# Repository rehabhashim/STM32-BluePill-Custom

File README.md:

# STM32-BluePill-Custom
KiCad project for a custom STM32F103C8T6 (Blue Pill) development board. The PCB layout focuses on practical hardware design principles, including power integrity, ground planes, and DFM rules.

Key technical details:

The design centers on the STM32F103C8T6 (ARM Cortex-M3) microcontroller driven by a 16MHz external crystal. For robust power distribution, I implemented solid copper pours for the VBUS and +3.3V nets to improve thermal and current handling, backed by a continuous GND pour across the board to ensure a solid return path and minimize EMI. Signal integrity was prioritized by placing individual 100nF decoupling capacitors directly at the MCU's VDD pins to reduce loop inductance, alongside a dedicated VDDA filter network utilizing a 120Ω ferrite bead and capacitors for clean ADC performance. Mechanically, the board's outline and edge cuts were explicitly engineered to properly overhang the USB-B Mini connector, preventing any physical clearance issues post-fabrication.

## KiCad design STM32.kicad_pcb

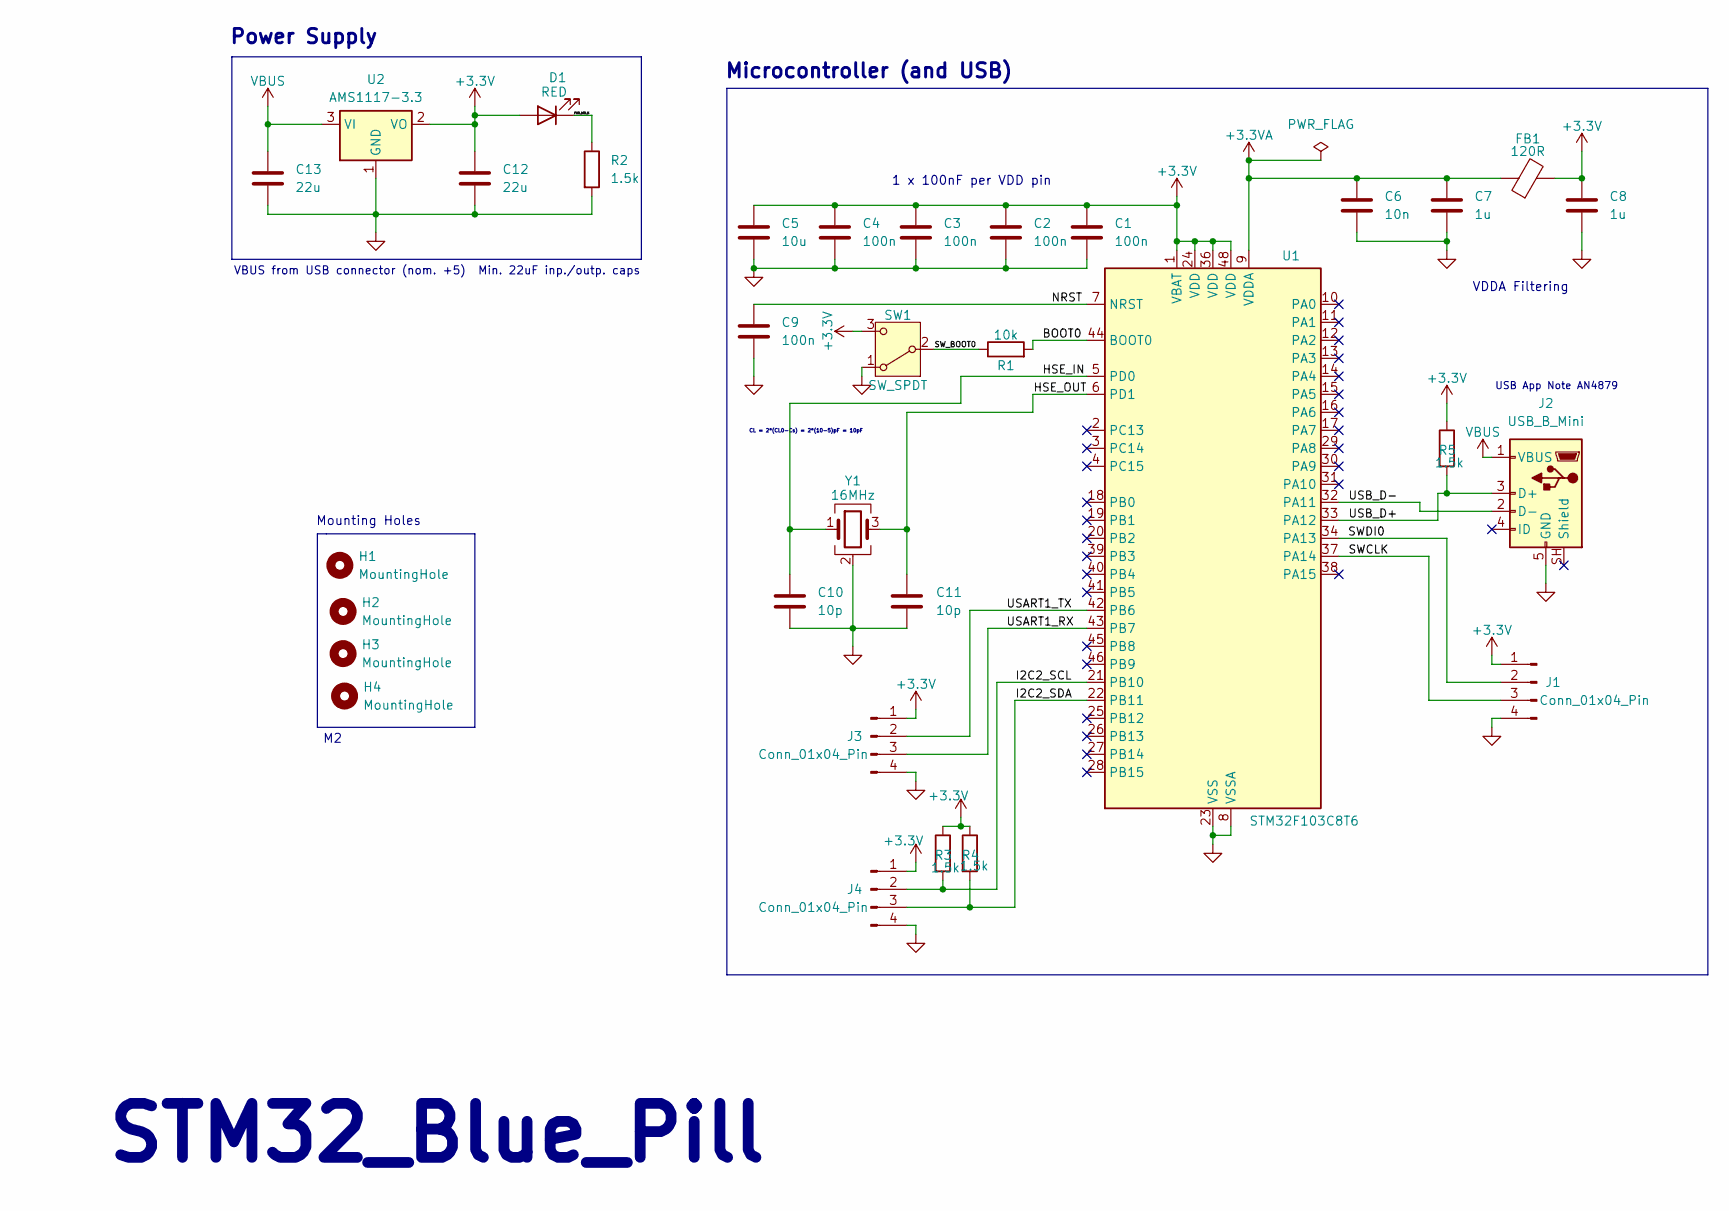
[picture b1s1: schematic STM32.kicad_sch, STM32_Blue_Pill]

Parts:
C1, C2, C3, C4, C9: 100n; C_0402_1005Metric
C5: 10u; C_0603_1608Metric
C6: 10n; C_0402_1005Metric
C7, C8: 1u; C_0402_1005Metric
C10, C11: 10p; C_0402_1005Metric
C12, C13: 22u; C_0805_2012Metric
D1: RED; LED_0603_1608Metric
FB1: 120R; L_0603_1608Metric
H1, H2, H3, H4: MountingHole; MountingHole_2.2mm_M2
J1, J3, J4: Conn_01x04_Pin; PinHeader_1x04_P2.54mm_Vertical
J2: USB_B_Mini; USB_Mini-B_Wuerth_65100516121_Horizontal
R1: 10k; R_0402_1005Metric
R2, R3, R4, R5: 1.5k; R_0402_1005Metric
SW1: SW_SPDT; SW_SPDT_PCM12
U1: STM32F103C8T6; LQFP-48_7x7mm_P0.5mm
U2: AMS1117-3.3; SOT-223-3_TabPin2
Y1: 16MHz; Crystal_SMD_3225-4Pin_3.2x2.5mm

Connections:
+3.3V: C1.1, C2.1, C3.1, C4.1, C5.1, C8.1, C12.1, D1.2 (A), FB1.2, J1.1, J3.1, J4.1, R3.1, R4.1, R5.1, SW1.3 (C), U1.1 (VBAT), U1.24 (VDD), U1.36 (VDD), U1.48 (VDD), U2.2 (VO)
+3.3VA: C6.1, C7.1, FB1.1, U1.9 (VDDA)
/BOOT0: R1.2, U1.44 (BOOT0)
/HSE_IN: C10.1, U1.5 (PD0), Y1.1
/HSE_OUT: C11.1, U1.6 (PD1), Y1.3
/I2C2_SCL: J4.2, R3.2, U1.21 (PB10)
/I2C2_SDA: J4.3, R4.2, U1.22 (PB11)
/NRST: C9.1, U1.7 (NRST)
/PWR_LED_K: D1.1 (K), R2.1
/SWCLK: J1.3, U1.37 (PA14)
/SWDI0: J1.2, U1.34 (PA13)
/SW_BOOT0: R1.1, SW1.2 (B)
/USART1_RX: J3.3, U1.43 (PB7)
/USART1_TX: J3.2, U1.42 (PB6)
/USB_D+: J2.3 (D+), R5.2, U1.33 (PA12)
/USB_D-: J2.2 (D-), U1.32 (PA11)
GND: C1.2, C2.2, C3.2, C4.2, C5.2, C6.2, C7.2, C8.2, C9.2, C10.2, C11.2, C12.2, C13.2, J1.4, J2.5 (GND), J3.4, J4.4, R2.2, SW1.1 (A), U1.8 (VSSA), U1.23 (VSS), U1.35 (VSS), U1.47 (VSS), U2.1 (GND), Y1.2 (G), Y1.4 (G)
VBUS: C13.1, J2.1 (VBUS), U2.3 (VI)

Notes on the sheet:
Microcontroller (and USB)
USB App Note AN4879
Mounting Holes
CL = 2*(CL0-Cs) = 2*(10-5)pF = 10pF
1 x 100nF per VDD pin
Power Supply
VDDA Filtering
STM32_Blue_Pill
VBUS from USB connector (nom. +5) Min. 22uF inp./outp. caps

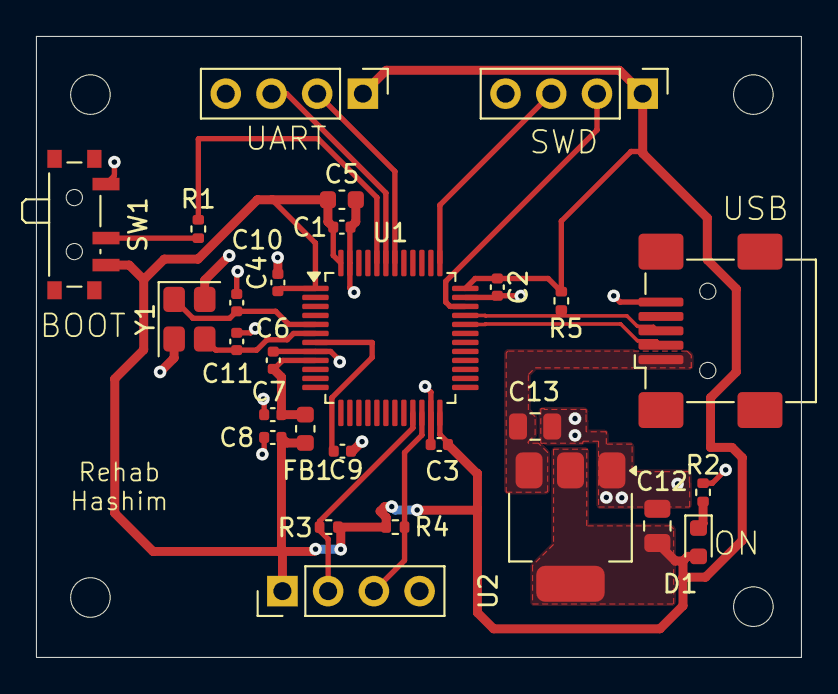
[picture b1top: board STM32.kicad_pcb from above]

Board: 2 copper layers, 42.5 x 34.5 mm, 32 parts (0 on the bottom side), 18 nets.
